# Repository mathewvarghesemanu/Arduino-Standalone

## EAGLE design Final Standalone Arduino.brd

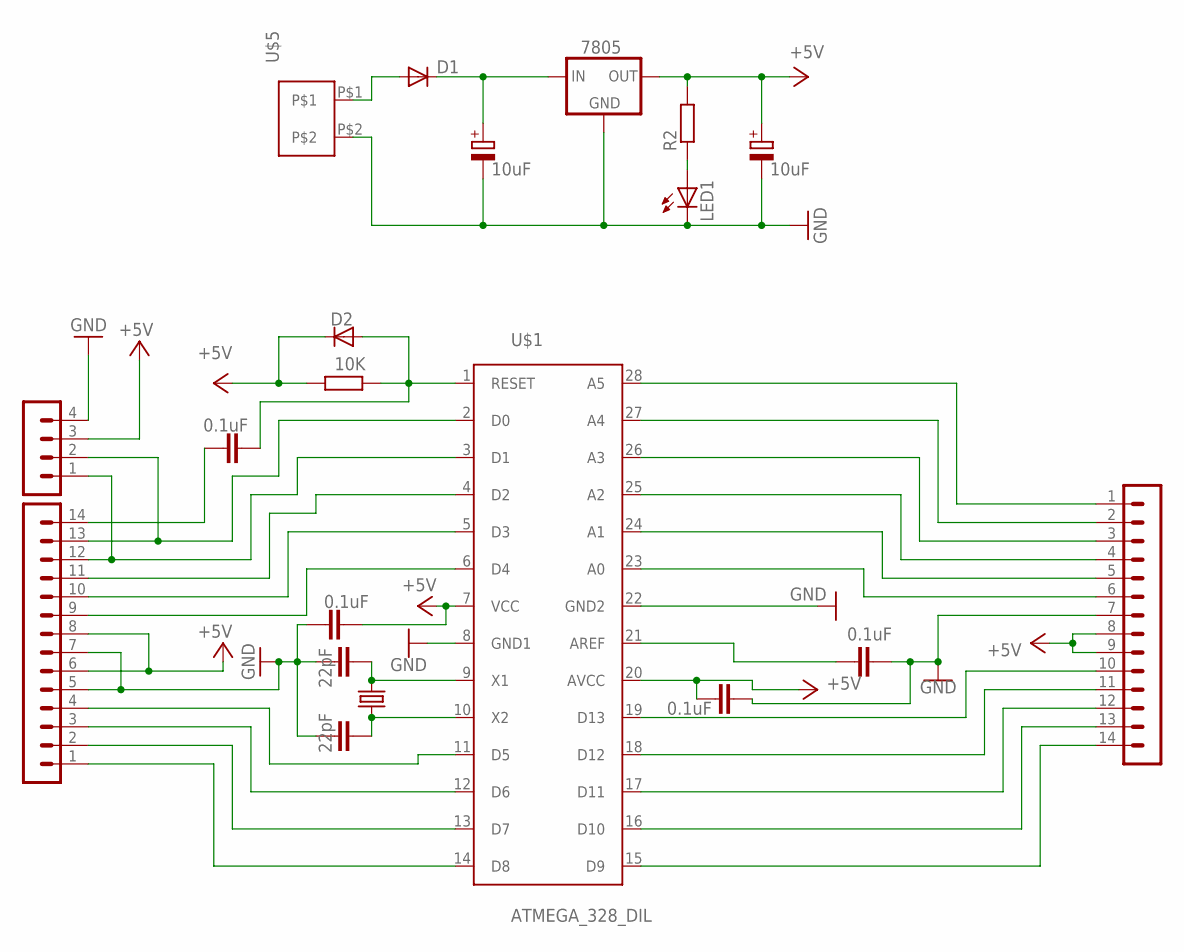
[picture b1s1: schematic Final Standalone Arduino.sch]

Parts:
C1, C2: 22pF; C025-024X044
C3, C5, C6, C7: 0.1uF; C025-024X044
C4, C9: 10uF; E2-5
D1, D2: DIODE-D-7.5; D-7.5
IC2: 7805; 78XXL
LED1: LED5MM
R1: 10K; 0207/10
R2: R-EU_0207/10; 0207/10
U$1: ATMEGA_328_DIL
U$2, U$3: 14_PIN_CONN
U$4: 4_PIN_CONN
U$5: 2_PIN_SCREW_CONN
Y1: CRYSTALHC49UV; HC49U-V

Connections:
9V: D1.A, U$5.P$1
+5V: C3.2, C5.2, C9.+, D2.C, IC2.OUT, R1.1, R2.2, U$1.7 (VCC), U$1.20 (AVCC), U$2.6, U$2.8, U$3.8, U$3.9, U$4.3
GND: C1.1, C2.1, C3.1, C4.-, C5.1, C7.1, C9.-, IC2.GND, LED1.K (C), U$1.8 (GND1), U$1.22 (GND2), U$2.5, U$2.7, U$3.7, U$4.4, U$5.P$2
unnamed: C6.2, D2.A, R1.2, U$1.1 (RESET)
unnamed: C1.2, U$1.9 (X1), Y1.2
unnamed: C2.2, U$1.10 (X2), Y1.1
unnamed: U$1.2 (D0), U$2.13, U$4.2
unnamed: U$1.3 (D1), U$2.12, U$4.1
unnamed: U$1.4 (D2), U$2.11
unnamed: C4.+, D1.C, IC2.IN
unnamed: U$1.6 (D4), U$2.9
unnamed: LED1.A, R2.1
unnamed: U$1.28 (A5), U$3.1
unnamed: U$1.27 (A4), U$3.2
unnamed: U$1.26 (A3), U$3.3
unnamed: U$1.25 (A2), U$3.4
unnamed: U$1.24 (A1), U$3.5
unnamed: U$1.23 (A0), U$3.6
unnamed: U$1.15 (D9), U$3.14
unnamed: U$1.16 (D10), U$3.13
unnamed: U$1.17 (D11), U$3.12
unnamed: U$1.18 (D12), U$3.11
unnamed: U$1.19 (D13), U$3.10
unnamed: U$1.14 (D8), U$2.1
unnamed: U$1.13 (D7), U$2.2
unnamed: U$1.12 (D6), U$2.3
unnamed: U$1.11 (D5), U$2.4
unnamed: C6.1, U$2.14
unnamed: U$1.5 (D3), U$2.10
unnamed: C7.2, U$1.21 (AREF)

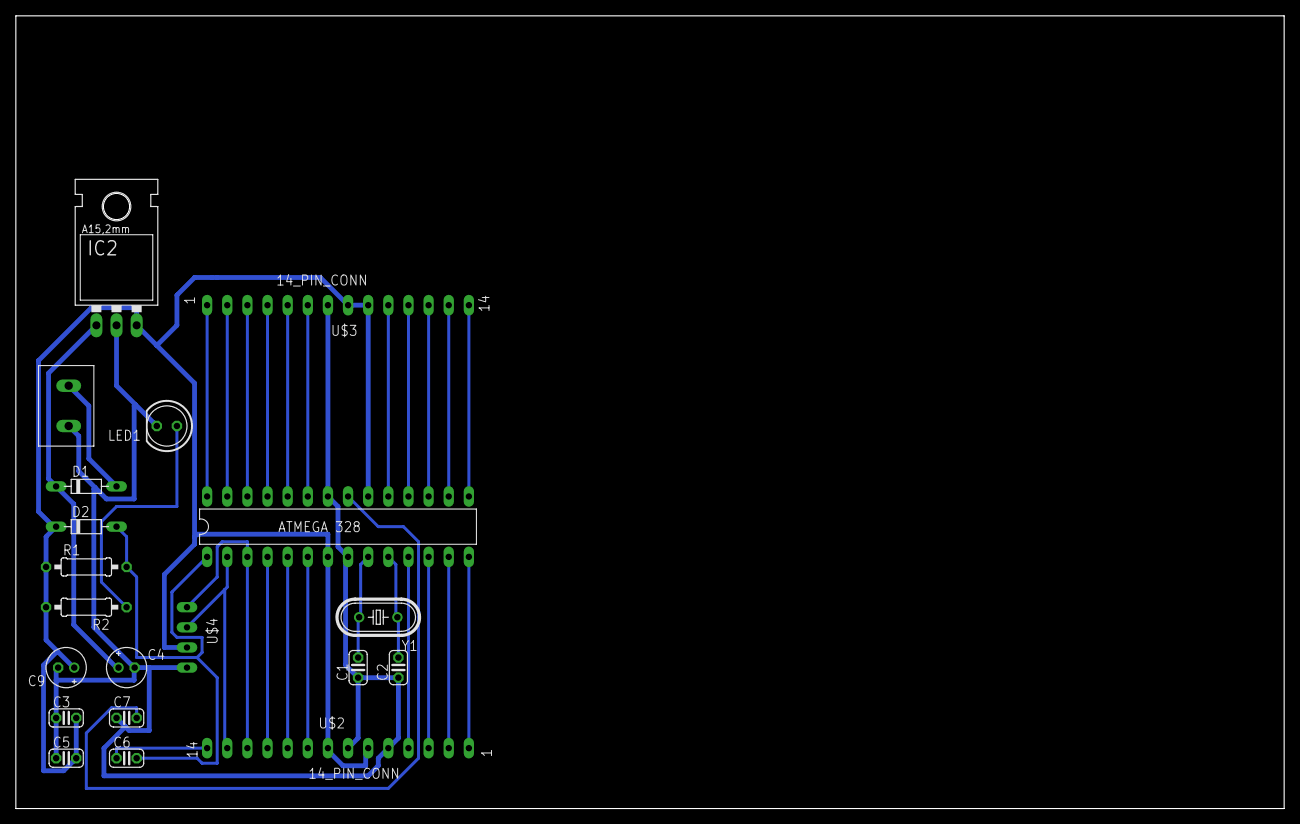
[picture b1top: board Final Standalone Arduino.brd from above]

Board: 2 copper layers, 160.0 x 100.0 mm, 20 parts (0 on the bottom side), 30 nets.

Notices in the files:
parts and their libraries:
SparkFun-FreqCtrl: Licensing: CC v3.0 Share-Alike You are welcome to use this library for commercial purposes.
